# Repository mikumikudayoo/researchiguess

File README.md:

# TAPH research software

TAPH investigates flow-dependent blade-pitch control for hydropower generators.
The revised software implements a fixed fuzzy schedule, an HTTP controller,
**uncalibrated synthetic simulations**, a disabled-by-default ESP32 adapter and a
reproducible historical data analysis. It does not establish physical protection,
hydraulic efficiency, optimized pitch, longer component life or prototype readiness.

The researchers' design requirement is **increasing intended physical blade pitch
with increasing volumetric flow**. Servo rotation, actual blade pitch and angle of
attack are different quantities. The configurable affine linkage remains physically
unverified; a reversed linkage can require decreasing servo commands for increasing
pitch. The example identity transform is not a calibration.

## Install and verify

Use the Bun version pinned in `package.json` (1.4.3), Git, and a C++17-capable `g++`
for host-only firmware tests. TypeScript is pinned to 5.9.3. GitHub Actions runs the
same software checks on Ubuntu.

```sh
bun install --frozen-lockfile
bun test
bun run typecheck
bun run build
```

Build is a bundling check. Use the source-based commands below from the repository
root to run research workflows; generated bundles are not standalone deployment
packages with embedded source/data manifests. No test flashes firmware, opens a
serial device or energizes equipment. Passing tests verifies the stated software
specification, not physical calibration or scientific validation.

## Choose an explicit evidence pathway

Every output directory must be new. Generated files are excluded from Git by
`results/`; retain completed run directories and their manifests together.

```sh
# Historical software replay, preserving original arithmetic and timing defects:
bun run legacy:simulate -- results/my-legacy-replay

# New corrected constant-flow illustration:
bun run simulate -- results/my-corrected-constant-run

# New dynamic-flow comparisons and plots:
bun run simulate:dynamics -- results/my-dynamic-run

# Reanalysis of the unchanged historical manuscript table:
bun run analyze:historical --input /path/to/power-table.csv \
  --source-manifest /path/to/source-manifest.json --out results/my-historical-reanalysis
```

The constant and dynamic commands accept an optional second positional argument
containing a complete JSON configuration. Their generated `config.json` can serve
as an explicit starting point for a new run. Configurations, source and output
hashes, runtime and software revision are recorded. Do not analyze an incomplete
manifest or treat a dirty source tree as identified solely by its commit hash.

| Evidence category | Meaning |
|---|---|
| `historical-reported-unverified` | Locally supplied reported power values; physical versus simulation origin remains unresolved |
| `historical-simulator-replay` | New execution of the byte-preserved audited synthetic code; not proof of the historical table's source |
| `corrected-synthetic-simulation` | Newly generated outputs from explicit assumed model/scenario/controller configurations |
| `physical-measurement` | Reserved for future documented acquisitions with raw records, instruments and calibration; none supplied here |

Firmware status/acquisition telemetry is labeled unverified bench telemetry and
must not be promoted to a validated physical experiment without a separate run and
calibration record. See [data provenance and analysis](docs/reproducibility.md).

## Historical preservation and entry points

The inspected default branch matched audited commit
`a37d1d5abf4d13d775ae206b4cd1c4c59f0e88ce` exactly before these six development
milestones. No intervening historical change was found. All original files remain
in that immutable commit. Byte-identical server/simulator archives, baseline
constants, rule schedules, RNG behavior and all 25 replay CSV fingerprints are
preserved and tested. See [baseline inventory](docs/baseline.md).

The historical server commands 10°,25°,40°,58°,75° at the five nominal flows;
the historical simulator uses 70°,55°,40°,25°,10°. Those records are not changed.
`simulator.ts` now refuses ambiguous direct execution and points to the explicit
commands above. It does not silently substitute a new schedule into an old run.
Legacy CSV `Measured_RPM` is synthetic speed; historical `Generated_Wattage_W`
includes the unexplained additional 0.65 factor after terminal VI.

`bun server.ts` starts the new versioned controller API on localhost with the
unverified identity mapping and hardware eligibility false. The retired numeric-only
route returns 410. Server and new simulations call the same fixed zero-order
Sugeno-style schedule; they do not learn, adapt parameters or discover an optimum.
See [physical coordinates, memberships, rules and protocol](docs/controller.md).

## What the new simulations establish

The corrected electrical boundary uses `PL = VI = I²RL = V²/RL`, with internal
copper loss separate. The initial row is the initial state at t=0, followed by
exact first-order transitions for held targets and explicit measurement windows.
The assumed 42° speed peak is built into the default plant law, not experimentally
discovered. No hydraulic head, torque or closed mechanical energy balance is modeled.
See [constant model assumptions and schema](docs/model.md).

Dynamic scenarios prescribe constant, step, ramp and bounded profile flow. True
flow reaches the plant; separately noisy sampled flow reaches the controller.
Communication delay, actuator time constant and rate limit are uncalibrated
settings. Fixed5, fixed42, increasing fuzzy and increasing linear comparisons
share inputs, initial conditions and windows. Requested, delivered and actual
modeled pitch remain separate. See [dynamic assumptions and metric definitions](docs/dynamics.md).

Outputs include unit-labeled CSV/JSON and reproducible SVGs. Speed, power, energy,
variability and finite-record settling describe the model. Seeds and correlated
time points are not independent physical observations. The model cannot establish
wear, lifespan, overspeed protection, real-time hardware performance or efficiency.

## Historical table reanalysis

The public repository intentionally does not bundle manuscript data, private source
links or their acquisition records. Supply the exact CSV and source manifest locally
as described in [the input schema](docs/reproducibility.md). The tool preserves all
listed values, records byte hashes and produces descriptive tables, SD denominators,
plots and a conditional paired calculation on five flow means. It does not infer
physical provenance, independent sampling or preserved output from a nonsignificant
result. The 25 listed values per condition are described separately; column positions
are not verified trial IDs. Automated tests use explicitly artificial fixtures,
never invented research observations.

## Firmware boundary

The root `sketch_aug3a.ino` stops compilation and points to the separate target
`firmware/esp32/taph_reliability/`. Default configuration initializes serial status
only: no GPIO, sensor, network, servo or relay. The optional operational path needs
private reviewed configuration, calibration records, fresh eligible commands,
explicit local arming and a separate pump command. It never automatically starts
the pump. No zero-angle or hold-last behavior is declared safe.

Portable C++ tests and fake adapter interfaces verify software timing, message
validation, stale data, latching and actuator/pump sequencing. Both firmware paths
also compile with the pinned real ESP32 toolchain, using an illustrative target
and a non-production fixture. This establishes build compatibility only; the
as-built board, wiring, PWM startup, measured linkage, sensor calibration and
supervised bench validation remain unverified. See the versions, target and limits in
[firmware gates and remaining work](docs/firmware.md). The unrelated `badapple.ino`
demo remains unchanged and is not part of the TAPH sketch or validation.

## Review status and next work

Six stacked PRs propose these changes; they were not merged automatically. Review
the PR chain in order. The complete software/documentation/model versus physical
validation classification is in [engineering traceability](docs/engineering-traceability.md).

Before physical deployment, resolve the historical data source, as-built board and
wiring, measured command-to-pitch transform, sensor calibration, physically justified
fault action, external interlock and compile compatibility with the confirmed
as-built board. Then perform a supervised,
recorded bench protocol and a fair fixed-pitch sweep with a predefined speed/power
objective. Narrow claims to the evidence available while those steps remain open.

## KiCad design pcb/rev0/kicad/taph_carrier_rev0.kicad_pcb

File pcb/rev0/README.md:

# TAPH ESP32 carrier PCB: rev 0 preliminary design package

**Status: PRELIMINARY DESIGN FOR REVIEW. NOT FOR FABRICATION, ASSEMBLY OR ENERGIZATION.**
Prepared 2026-11-07 for the research adviser/consultant meeting on 2026-11-08. The board must not be
represented as manufacturable or safe to power until the actual components and this design have been
reviewed. A clean ERC/DRC is not proof of operational safety.

## What this is

A native, editable **KiCad 10** project for a modular two-layer carrier board. The board takes a socketed
classic-ESP32 development board (provisionally an Espressif ESP32-DevKitC V4, **to be confirmed**) and
provides:

* externally supplied low-voltage DC inputs, each a separate isolation point: logic, pump and servo;
* input protection and a 5 V regulator module for logic;
* a pump switch that is **off by hardware default**, with a hardware enable jumper;
* a buffered servo PWM output with its own supply entry;
* a flow sensor input plus optional RPM and pitch-feedback inputs;
* a generator voltage-sense input and a generator current-sensor interface (analog or I2C);
* separate pump current and pump supply-voltage measurement;
* an OLED (I2C) socket, I2C expansion and spare GPIO;
* 20 labelled test points.

No mains voltage is routed on the PCB, and generator power does not pass through it.

## Package contents

| Path | Content |
|---|---|
| `kicad/taph_carrier_rev0.kicad_pro` | KiCad project (open this) |
| `kicad/*.kicad_sch` | Hierarchical schematic: root architecture sheet + 7 block sheets |
| `kicad/taph_carrier_rev0.kicad_pcb` | Preliminary 2-layer layout (130 × 100 mm, provisional) |
| `kicad/libs/TAPH_Rev0.kicad_sym` | Project-local symbols for the two DevKitC header sockets (stock footprints) |
| `exports/taph_carrier_rev0_schematic.pdf` | **Schematic for review** (8 pages) |
| `exports/pcb/pcb_top_layers.png/.svg/.pdf`, `pcb_bottom_layers_mirrored.*`, `pcb_assembly_view_top.*` | 2-D layer views |
| `exports/pcb/render_top.png`, `render_bottom.png`, `render_iso.png` | 3-D renders (appearance only) |
| `exports/taph_carrier_rev0_kicad_bom.csv` | KiCad-exported grouped BOM with Status / candidate part / review-note fields |
| `exports/erc_report.txt`, `exports/drc_report.txt`, `exports/routing_report.json` | Verification output |
| `docs/architecture.md` | **Electrical architecture explanation** (domains, protection, default-off, front ends, layout status) |
| `docs/gpio_map.md` | **Proposed GPIO map** and the reasons for each pin |
| `docs/bom_review.md` / `.csv` | **Component list**, each part's status: implemented, provisional, TBD, optional, DNP or confirm |
| `docs/verification.md` | **ERC/DRC results**, blockers and assumptions that need physical confirmation |
| `docs/questions_for_review.md` | **Questions for the adviser and consultant** |
| `docs/review_log.md` | Review findings received (R1: independent review of PR #8) with technical responses and proposed, not yet applied, actions |
| `tools/` | Generators (`design.py` is the single source of design intent) and the build/export scripts |

## Designed versus conceptual

| Item | State |
|---|---|
| Schematic topology of every block | **Designed.** Electrically coherent; ERC 0 errors / 0 warnings; exported netlist verified pin-by-pin against intent |
| Logic power chain, ESP32 sockets, pump gate drive and default-off, servo buffer, pulse-input and ADC conditioning, I2C/OLED, test points | **Designed** with chosen values; candidate parts still need datasheet confirmation |
| Logic/signal/analog routing | **Preliminary.** All 38 non-blocked nets auto-routed by a simple project router; not hand-optimised |
| Board DRC | **Not clean.** 35 unconnected items (blocked pump/servo nets), 4 starved-thermal errors and 2 silkscreen warnings remain open (`docs/verification.md`) |
| Pump power path, servo power path | **Placed, routing BLOCKED.** Widths, fuses, MOSFET and shunt depend on unmeasured currents |
| Generator voltage divider, shunt value, INA180 gain, fuse ratings, servo bulk capacitor, TVS on servo/generator inputs | **TBD** (placeholder values); blocked on external specifications |
| RPM and pitch-feedback inputs, I2C expansion, spare GPIO | **Optional** interfaces; sensors not chosen |
| Mechanical safe state of the blade/servo; generator electrical characteristics | **Conceptual / unresolved.** Not claimed by this board |
| Dev board identity, pinout, row spacing, antenna position; enclosure and mounting | **To be confirmed** physically |
| Firmware support for the new channels and this GPIO map | **Not started.** The existing firmware is unchanged |

## Reference sources and how they were used

* **Rev-0 architecture:** the requirement list in the research director's brief of 2026-11-07. A separate
  "PCB architecture rev 0" file is not present in the repository. See `docs/architecture.md` §1.
* **Historical firmware** (`sketch_aug3a.ino` at `a37d1d5`): an inventory of functions only. Its pin
  assignments are not treated as evidence of wiring; several are strapping pins and were changed.
* **Current reliability adapter** (`firmware/esp32/taph_reliability`): interface requirements (pull-up
  pulse input, raw ADC current, reviewed inactive pump level, servo PWM). Its pins stay unconfigured.
* **Tinkercad conceptual drawing:** described in audit finding F10 (Uno with substitute symbols, such
  as a PIR for the flow sensor). Treated as a conceptual block list only; its wires are not authoritative.

## Reproduce

Requires KiCad 10 (`kicad-cli` and KiCad's bundled Python with `pcbnew`) and Python 3 for the
schematic generator:

```bash
bash pcb/rev0/tools/build.sh
```

```bash
bash pcb/rev0/tools/export.sh
```

`build.sh` regenerates the symbols, project, schematic and board from `tools/design.py` and
`tools/gen_pcb.py`, then runs ERC, the netlist cross-check and DRC. The generators are deterministic
(stable UUIDs). If the design is edited by hand in KiCad, treat the KiCad files as the source of truth and
stop regenerating them.

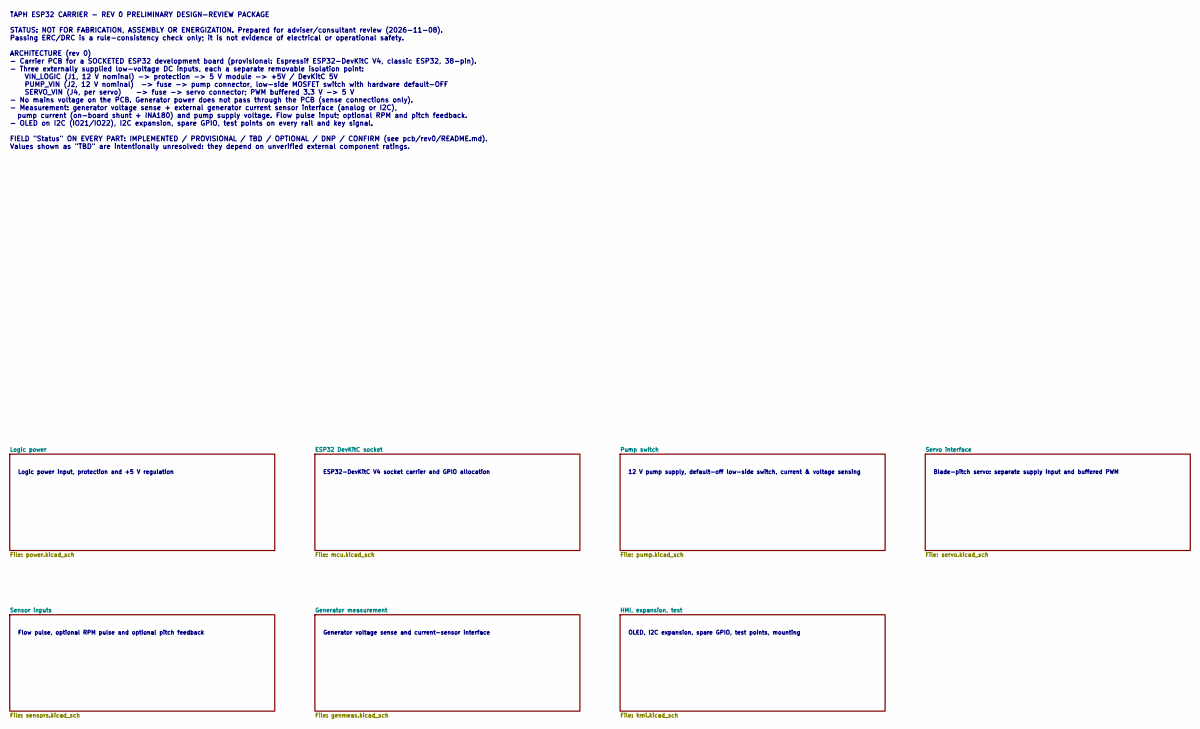
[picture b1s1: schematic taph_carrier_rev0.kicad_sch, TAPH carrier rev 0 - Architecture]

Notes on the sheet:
TAPH ESP32 CARRIER - REV 0 PRELIMINARY DESIGN-REVIEW PACKAGE STATUS: NOT FOR FABRICATION, ASSEMBLY OR ENERGIZATION. Prepared for adviser/consultant review (2026-11-08). Passing ERC/DRC is a rule-consistency check only; it is not evidence of electrical or operational safety. ARCHITECTURE (rev 0) - C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
Logic power input, protection and +5 V regulation
ESP32-DevKitC V4 socket carrier and GPIO allocation
12 V pump supply, default-off low-side switch, current & voltage sensing
Blade-pitch servo: separate supply input and buffered PWM
Flow pulse, optional RPM pulse and optional pitch feedback
Generator voltage sense and current-sensor interface
OLED, I2C expansion, spare GPIO, test points, mounting

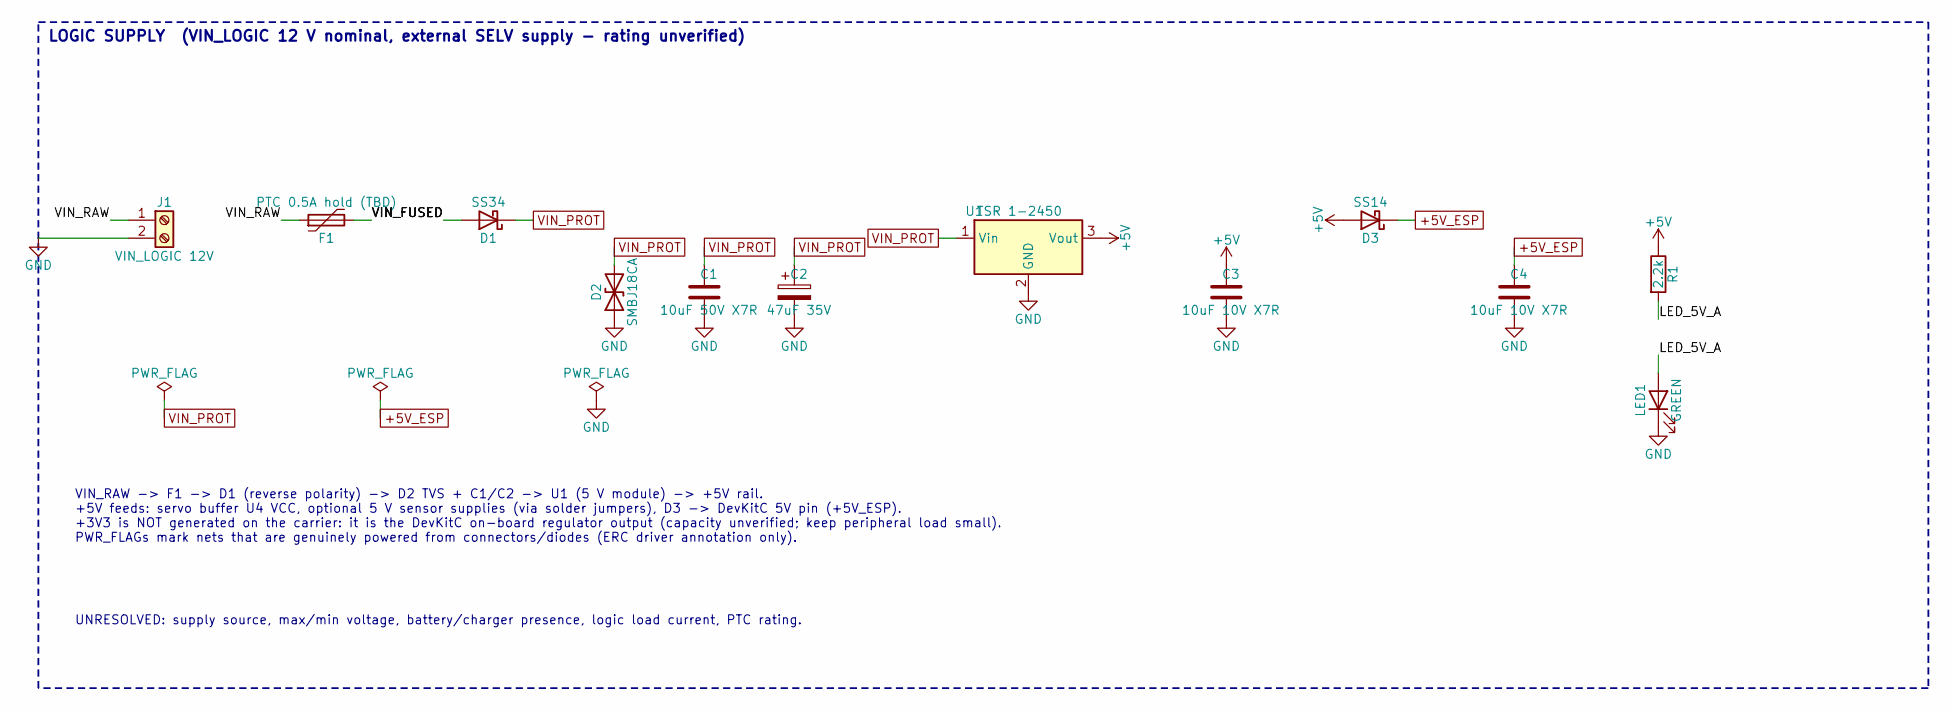
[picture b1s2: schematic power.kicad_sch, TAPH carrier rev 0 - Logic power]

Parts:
C1: 10uF 50V X7R; C_1210_3225Metric
C2: 47uF 35V; CP_Elec_6.3x7.7
C3, C4: 10uF 10V X7R; C_1206_3216Metric
D1: SS34; D_SMA; MPN_candidate SS34 (candidate, 40 V 3 A class - verif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
D2: SMBJ18CA; D_SMB; MPN_candidate SMBJ18CA (candidate - verify clamp vs U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
D3: SS14; D_SMA; MPN_candidate SS14 (candidate)
F1: PTC 0.5A hold (TBD); Fuse_1812_4532Metric
J1: VIN_LOGIC 12V; TerminalBlock_Phoenix_MKDS-1,5-2-5.08_1x02_P5.08mm_Horizont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; MPN_candidate Phoenix MKDS 1,5/2-5,08 (candidate)
LED1: GREEN; LED_0805_2012Metric
R1: 2.2k; R_0805_2012Metric
U1: TSR 1-2450; Converter_DCDC_TRACO_TSR-1_THT; MPN_candidate TRACO TSR 1-2450 (candidate)

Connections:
+5V: C3.1, D3.2 (A), R1.1, U1.3 (Vout); also elsewhere on the board
+5V_ESP: C4.1, D3.1 (K); also elsewhere on the board
/Logic power/LED_5V_A: LED1.2 (A), R1.2
/Logic power/VIN_FUSED: D1.2 (A), F1.2
/Logic power/VIN_RAW: F1.1, J1.1
GND: C1.2, C2.2, C3.2, C4.2, D2.1 (A1), J1.2, LED1.1 (K), U1.2 (GND); also elsewhere on the board
VIN_PROT: C1.1, C2.1, D1.1 (K), D2.2 (A2), U1.1 (Vin); also elsewhere on the board

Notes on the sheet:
LOGIC SUPPLY (VIN_LOGIC 12 V nominal, external SELV supply - rating unverified)
VIN_RAW -> F1 -> D1 (reverse polarity) -> D2 TVS + C1/C2 -> U1 (5 V module) -> +5V rail. +5V feeds: servo buffer U4 VCC, optional 5 V sensor supplies (via solder jumpers), D3 -> DevKitC 5V pin (+5V_ESP). +3V3 is NOT generated on the carrier: it is the DevKitC on-board regulator output (capacity unv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
UNRESOLVED: supply source, max/min voltage, battery/charger presence, logic load current, PTC rating.

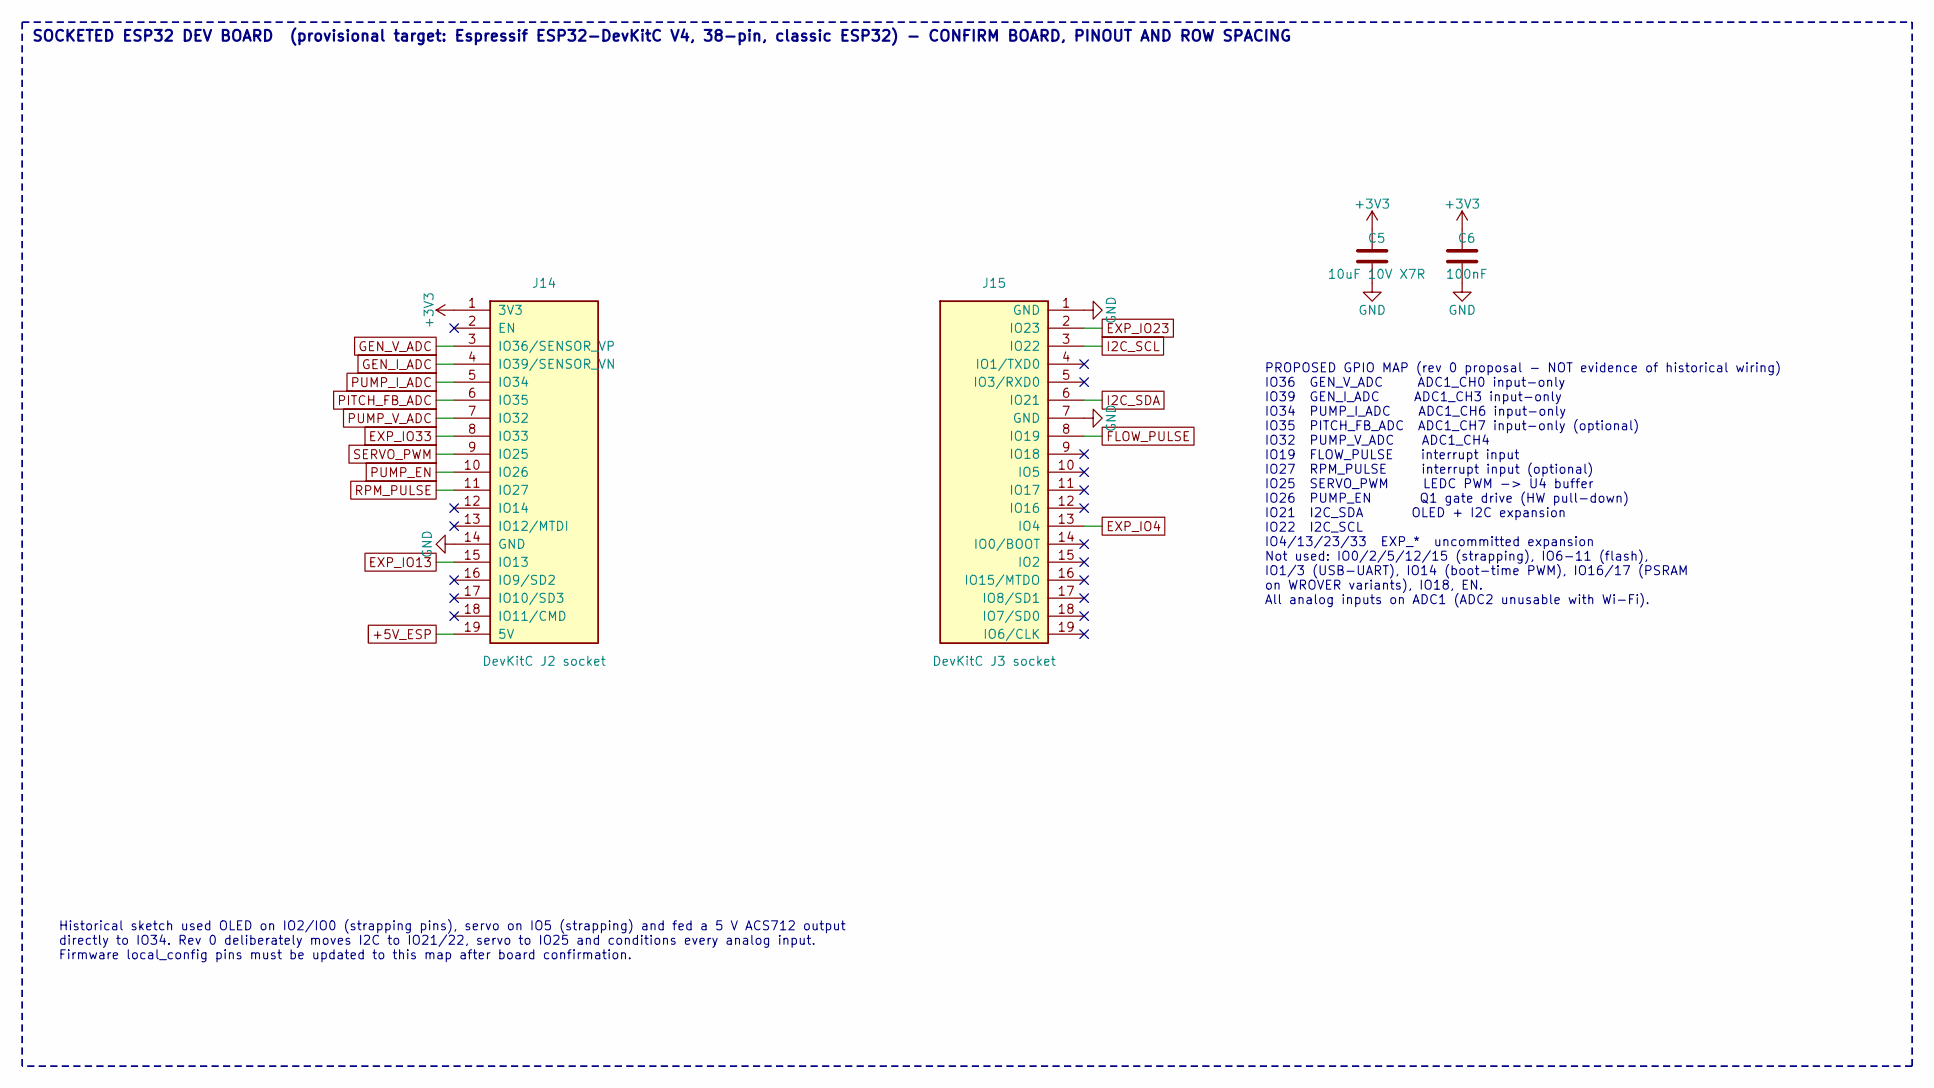
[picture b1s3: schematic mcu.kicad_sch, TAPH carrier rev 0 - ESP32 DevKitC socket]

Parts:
C5: 10uF 10V X7R; C_1206_3216Metric
C6: 100nF; C_0805_2012Metric
J14: DevKitC J2 socket; PinSocket_1x19_P2.54mm_Vertical; MPN_candidate 2.54 mm 1x19 female header
J15: DevKitC J3 socket; PinSocket_1x19_P2.54mm_Vertical; MPN_candidate 2.54 mm 1x19 female header

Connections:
+3V3: C5.1, C6.1, J14.1 (3V3); also elsewhere on the board
+5V_ESP: J14.19 (5V); also elsewhere on the board
EXP_IO4: J15.13 (IO4); also elsewhere on the board
EXP_IO13: J14.15 (IO13); also elsewhere on the board
EXP_IO23: J15.2 (IO23); also elsewhere on the board
EXP_IO33: J14.8 (IO33); also elsewhere on the board
FLOW_PULSE: J15.8 (IO19); also elsewhere on the board
GEN_I_ADC: J14.4 (IO39/SENSOR_VN); also elsewhere on the board
GEN_V_ADC: J14.3 (IO36/SENSOR_VP); also elsewhere on the board
GND: C5.2, C6.2, J14.14 (GND), J15.1 (GND), J15.7 (GND); also elsewhere on the board
I2C_SCL: J15.3 (IO22); also elsewhere on the board
I2C_SDA: J15.6 (IO21); also elsewhere on the board
PITCH_FB_ADC: J14.6 (IO35); also elsewhere on the board
PUMP_EN: J14.10 (IO26); also elsewhere on the board
PUMP_I_ADC: J14.5 (IO34); also elsewhere on the board
PUMP_V_ADC: J14.7 (IO32); also elsewhere on the board
RPM_PULSE: J14.11 (IO27); also elsewhere on the board
SERVO_PWM: J14.9 (IO25); also elsewhere on the board

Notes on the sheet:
SOCKETED ESP32 DEV BOARD (provisional target: Espressif ESP32-DevKitC V4, 38-pin, classic ESP32) - CONFIRM BOARD, PINOUT AND ROW SPACING
PROPOSED GPIO MAP (rev 0 proposal - NOT evidence of historical wiring) IO36 GEN_V_ADC ADC1_CH0 input-only IO39 GEN_I_ADC ADC1_CH3 input-only IO34 PUMP_I_ADC ADC1_CH6 input-only IO35 PITCH_FB_ADC ADC1_CH7 input-only (optional) IO32 PUMP_V_ADC ADC1_CH4 IO19 FLOW_PULSE interrupt input IO27 RPM_PULSE i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
Historical sketch used OLED on IO2/IO0 (strapping pins), servo on IO5 (strapping) and fed a 5 V ACS712 output directly to IO34. Rev 0 deliberately moves I2C to IO21/22, servo to IO25 and conditions every analog input. Firmware local_config pins must be updated to this map after board confirmation.

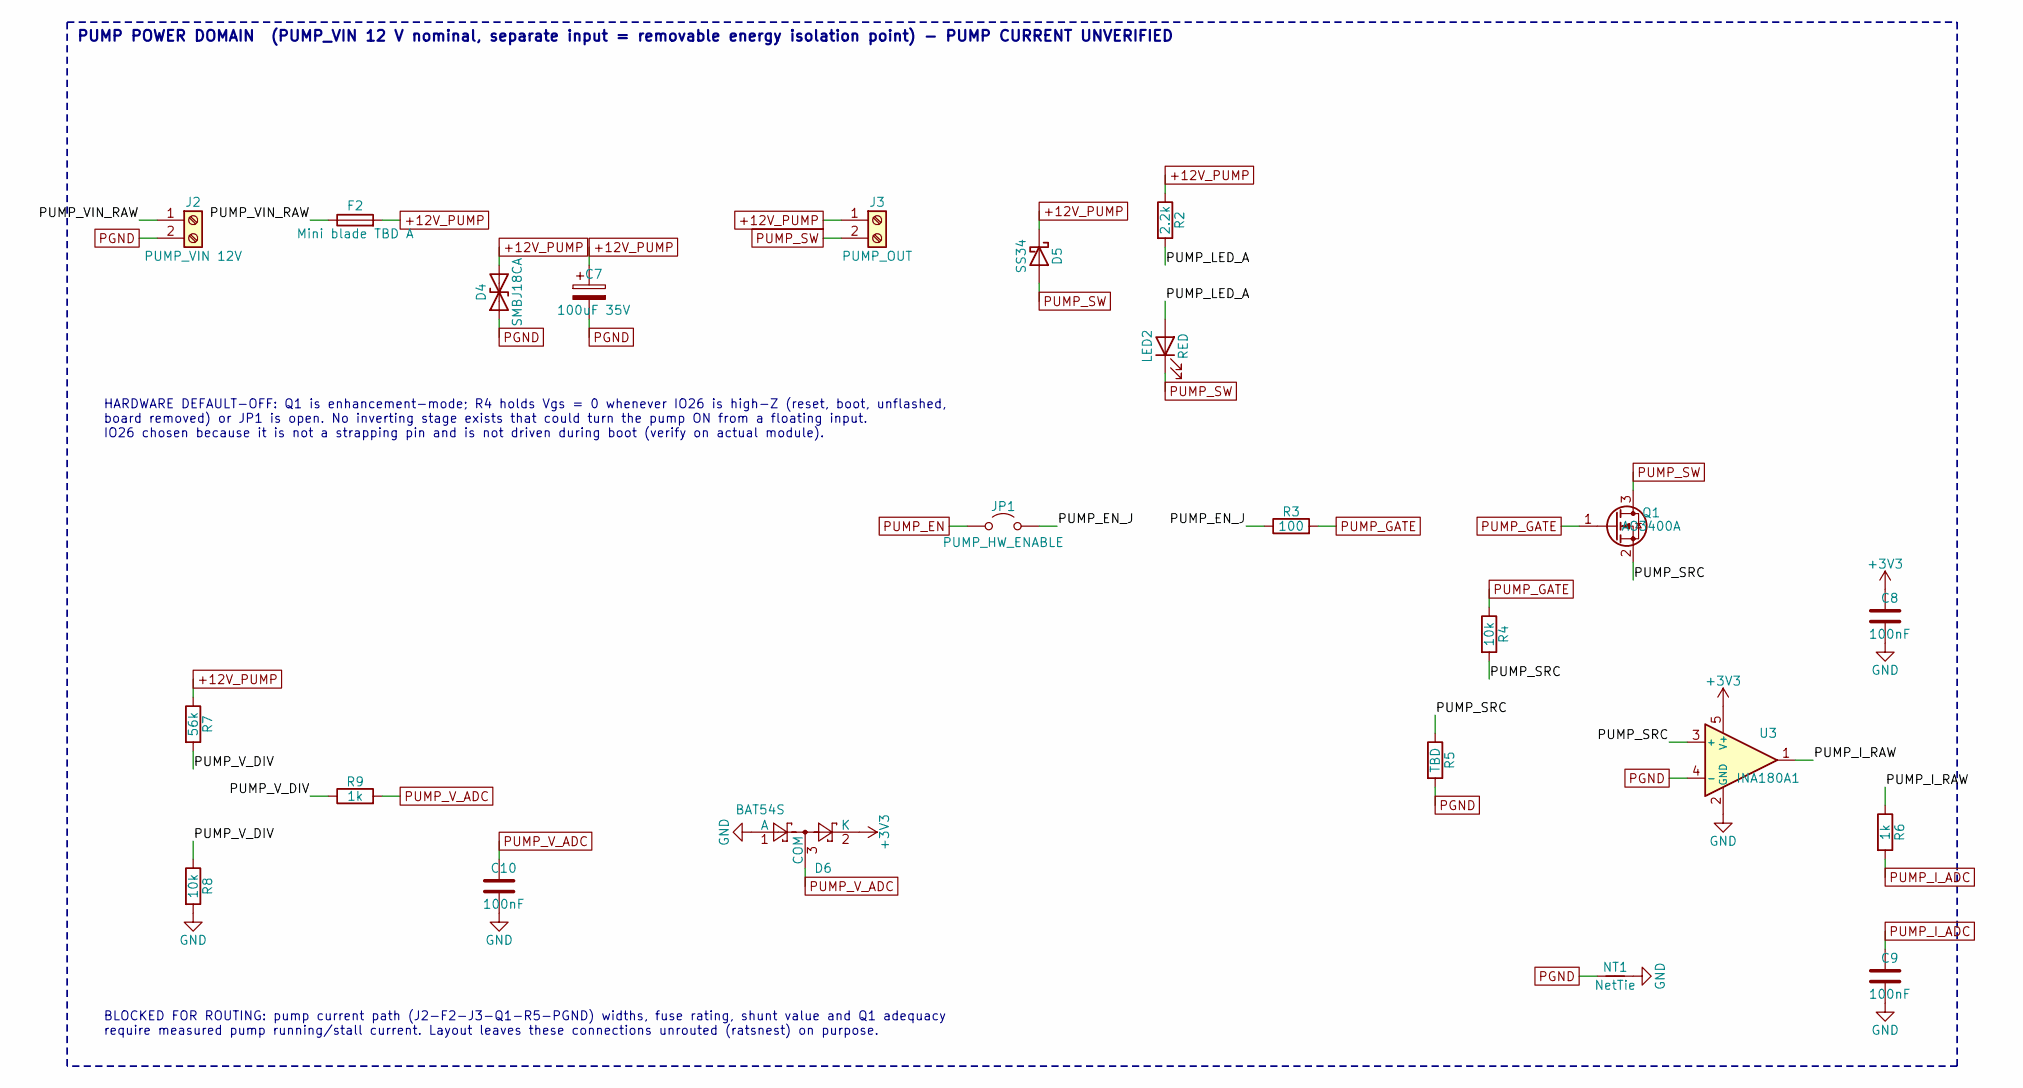
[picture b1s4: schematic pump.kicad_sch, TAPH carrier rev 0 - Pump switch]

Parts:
C7: 100uF 35V; CP_Elec_8x10
C8, C9, C10: 100nF; C_0805_2012Metric
D4: SMBJ18CA; D_SMB; MPN_candidate SMBJ18CA (candidate)
D5: SS34; D_SMA; MPN_candidate SS34 (candidate)
D6: BAT54S; SOT-23; MPN_candidate BAT54S (candidate)
F2: Mini blade TBD A; Fuseholder_Blade_Mini_Keystone_3568; MPN_candidate Keystone 3568 holder (candidate)
J2: PUMP_VIN 12V; TerminalBlock_Phoenix_MKDS-1,5-2-5.08_1x02_P5.08mm_Horizont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; MPN_candidate Phoenix MKDS 1,5/2-5,08 (candidate)
J3: PUMP_OUT; TerminalBlock_Phoenix_MKDS-1,5-2-5.08_1x02_P5.08mm_Horizont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; MPN_candidate Phoenix MKDS 1,5/2-5,08 (candidate)
JP1: PUMP_HW_ENABLE; PinHeader_1x02_P2.54mm_Vertical; MPN_candidate 2-pin header + shunt
LED2: RED; LED_0805_2012Metric
NT1: NetTie; NetTie-2_SMD_Pad2.0mm
Q1: AO3400A; SOT-23; MPN_candidate AO3400A (candidate)
R2: 2.2k; R_0805_2012Metric
R3: 100; R_0805_2012Metric
R4, R8: 10k; R_0805_2012Metric
R5: TBD; R_2512_6332Metric
R6, R9: 1k; R_0805_2012Metric
R7: 56k; R_0805_2012Metric
U3: INA180A1; SOT-23-5; MPN_candidate TI INA180A1 (candidate)

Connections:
+3V3: C8.1, D6.2 (K), U3.5 (V+); also elsewhere on the board
+12V_PUMP: C7.1, D4.2 (A2), D5.1 (K), F2.2, J3.1, R2.1, R7.1; also elsewhere on the board
/Pump switch/PUMP_EN_J: JP1.2 (B), R3.1
/Pump switch/PUMP_I_RAW: R6.1, U3.1
/Pump switch/PUMP_LED_A: LED2.2 (A), R2.2
/Pump switch/PUMP_SRC: Q1.2 (S), R4.2, R5.1, U3.3 (+)
/Pump switch/PUMP_VIN_RAW: F2.1, J2.1
/Pump switch/PUMP_V_DIV: R7.2, R8.1, R9.1
GND: C8.2, C9.2, C10.2, D6.1 (A), NT1.2, R8.2, U3.2 (GND); also elsewhere on the board
PGND: C7.2, D4.1 (A1), J2.2, NT1.1, R5.2, U3.4 (-); also elsewhere on the board
PUMP_EN: JP1.1 (A); also elsewhere on the board
PUMP_GATE: Q1.1 (G), R3.2, R4.1; also elsewhere on the board
PUMP_I_ADC: C9.1, R6.2; also elsewhere on the board
PUMP_SW: D5.2 (A), J3.2, LED2.1 (K), Q1.3 (D); also elsewhere on the board
PUMP_V_ADC: C10.1, D6.3 (COM), R9.2; also elsewhere on the board

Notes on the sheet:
PUMP POWER DOMAIN (PUMP_VIN 12 V nominal, separate input = removable energy isolation point) - PUMP CURRENT UNVERIFIED
HARDWARE DEFAULT-OFF: Q1 is enhancement-mode; R4 holds Vgs = 0 whenever IO26 is high-Z (reset, boot, unflashed, board removed) or JP1 is open. No inverting stage exists that could turn the pump ON from a floating input. IO26 chosen because it is not a strapping pin and is not driven during boot (ve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
BLOCKED FOR ROUTING: pump current path (J2-F2-J3-Q1-R5-PGND) widths, fuse rating, shunt value and Q1 adequacy require measured pump running/stall current. Layout leaves these connections unrouted (ratsnest) on purpose.

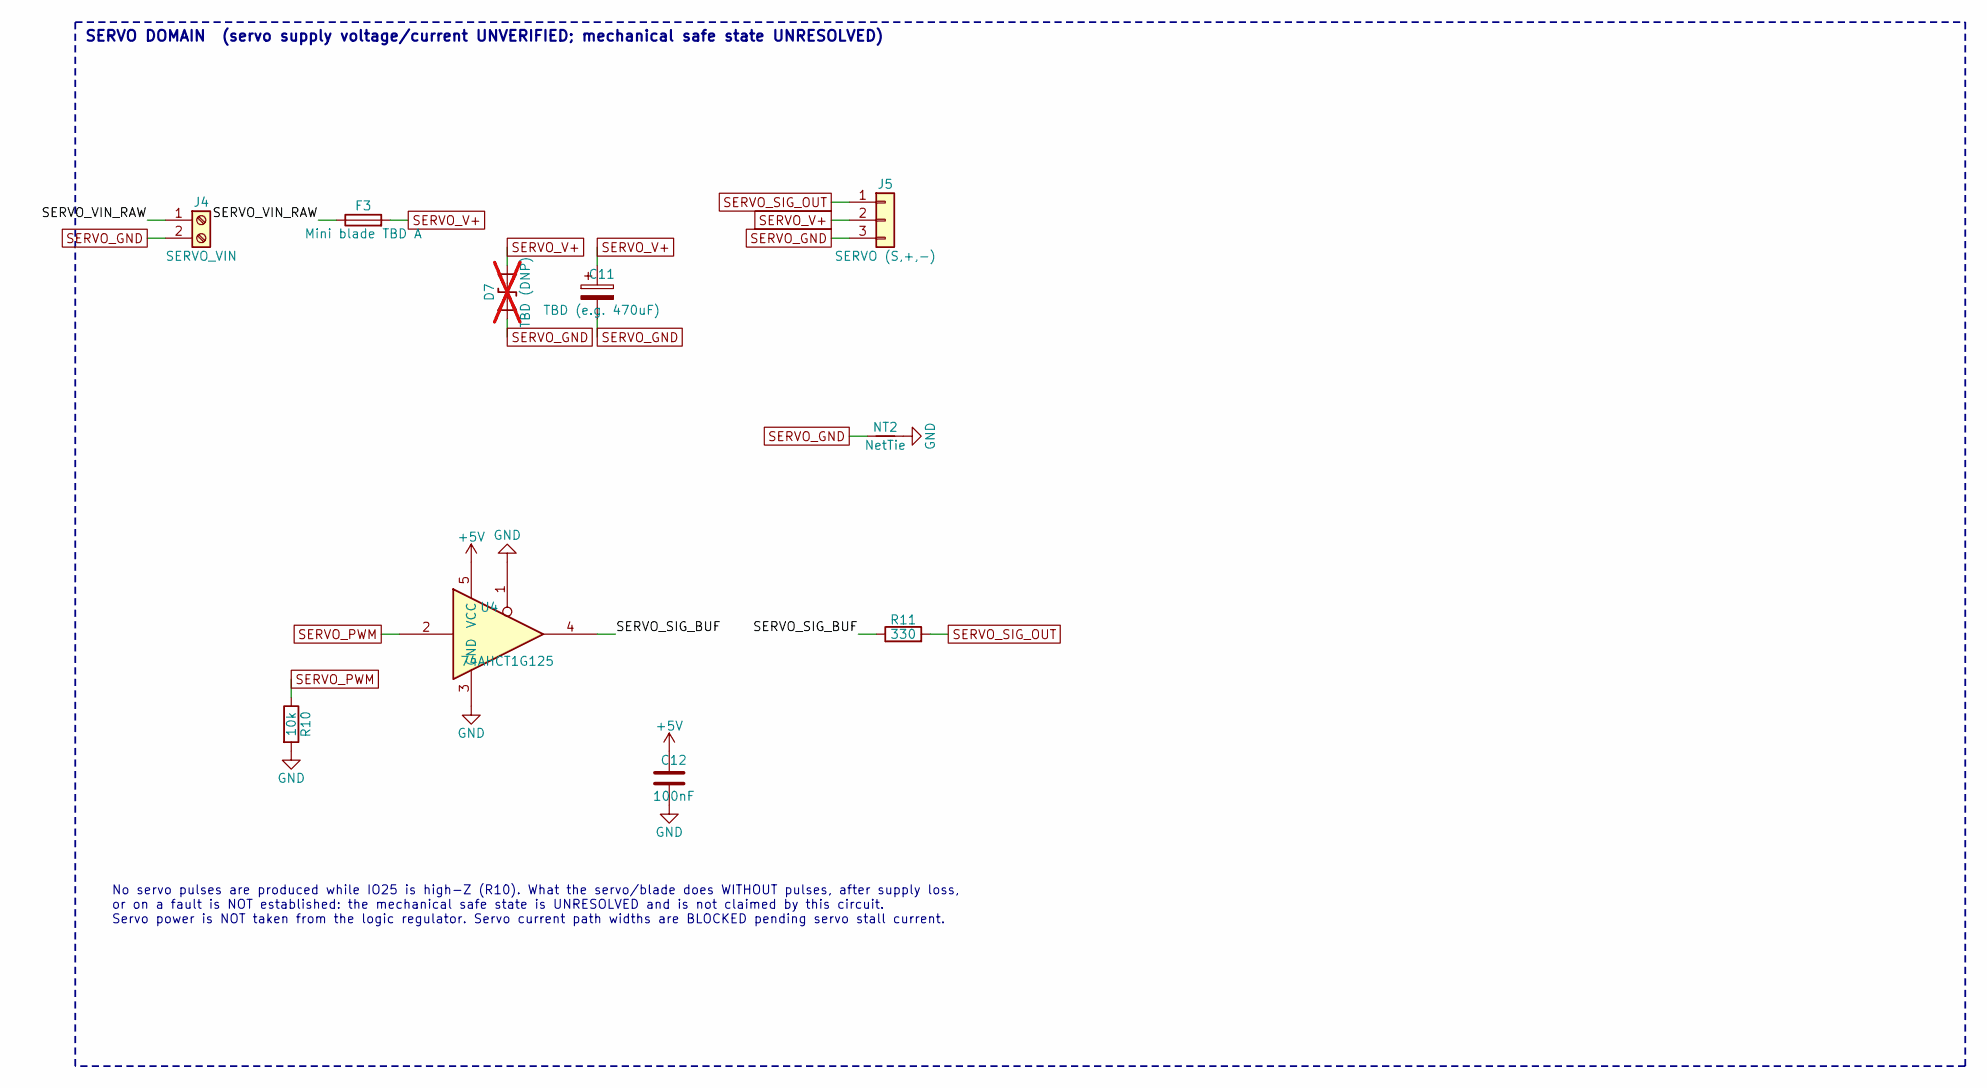
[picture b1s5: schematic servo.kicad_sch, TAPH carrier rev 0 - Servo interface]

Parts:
C11: TBD (e.g. 470uF); CP_Elec_8x10
C12: 100nF; C_0805_2012Metric
D7: TBD (DNP); D_SMB; not fitted
F3: Mini blade TBD A; Fuseholder_Blade_Mini_Keystone_3568; MPN_candidate Keystone 3568 holder (candidate)
J4: SERVO_VIN; TerminalBlock_Phoenix_MKDS-1,5-2-5.08_1x02_P5.08mm_Horizont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; MPN_candidate Phoenix MKDS 1,5/2-5,08 (candidate)
J5: SERVO (S,+,-); PinHeader_1x03_P2.54mm_Vertical
NT2: NetTie; NetTie-2_SMD_Pad2.0mm
R10: 10k; R_0805_2012Metric
R11: 330; R_0805_2012Metric
U4: 74AHCT1G125; SOT-23-5; MPN_candidate 74AHCT1G125 SOT-23-5 (candidate)

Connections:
+5V: C12.1, U4.5 (VCC); also elsewhere on the board
/Servo interface/SERVO_SIG_BUF: R11.1, U4.4
/Servo interface/SERVO_VIN_RAW: F3.1, J4.1
GND: C12.2, NT2.2, R10.2, U4.1, U4.3 (GND); also elsewhere on the board
SERVO_GND: C11.2, D7.1 (A1), J4.2, J5.3, NT2.1; also elsewhere on the board
SERVO_PWM: R10.1, U4.2; also elsewhere on the board
SERVO_SIG_OUT: J5.1, R11.2; also elsewhere on the board
SERVO_V+: C11.1, D7.2 (A2), F3.2, J5.2; also elsewhere on the board

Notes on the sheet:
SERVO DOMAIN (servo supply voltage/current UNVERIFIED; mechanical safe state UNRESOLVED)
No servo pulses are produced while IO25 is high-Z (R10). What the servo/blade does WITHOUT pulses, after supply loss, or on a fault is NOT established: the mechanical safe state is UNRESOLVED and is not claimed by this circuit. Servo power is NOT taken from the logic regulator. Servo current path w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

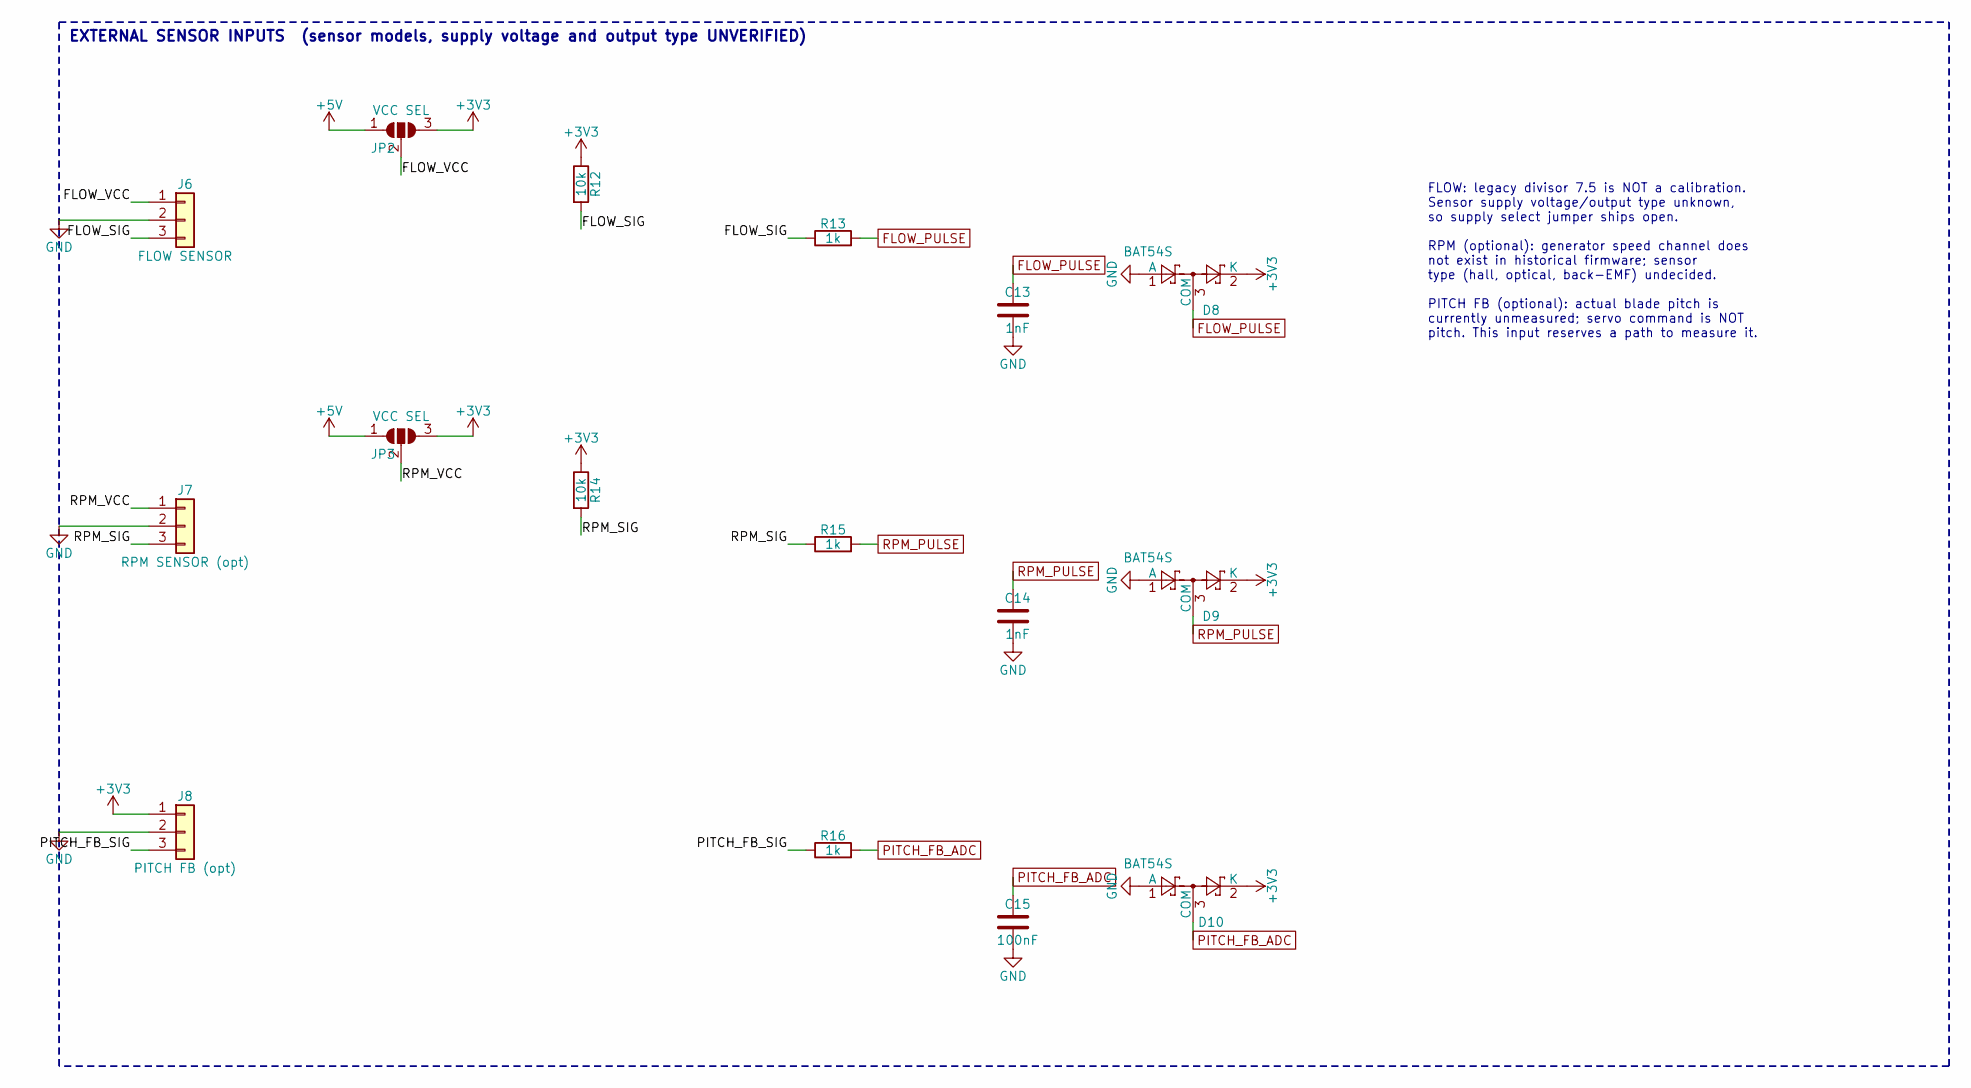
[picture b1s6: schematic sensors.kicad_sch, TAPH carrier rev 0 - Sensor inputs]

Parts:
C13, C14: 1nF; C_0805_2012Metric
C15: 100nF; C_0805_2012Metric
D8, D9, D10: BAT54S; SOT-23; MPN_candidate BAT54S (candidate)
J6: FLOW SENSOR; JST_XH_B3B-XH-A_1x03_P2.50mm_Vertical; MPN_candidate JST XH 3-pin (candidate)
J7: RPM SENSOR (opt); JST_XH_B3B-XH-A_1x03_P2.50mm_Vertical; MPN_candidate JST XH 3-pin (candidate)
J8: PITCH FB (opt); JST_XH_B3B-XH-A_1x03_P2.50mm_Vertical; MPN_candidate JST XH 3-pin (candidate)
JP2, JP3: VCC SEL; SolderJumper-3_P1.3mm_Open_RoundedPad1.0x1.5mm
R12, R14: 10k; R_0805_2012Metric
R13, R15, R16: 1k; R_0805_2012Metric

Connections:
+3V3: D8.2 (K), D9.2 (K), D10.2 (K), J8.1, JP2.3 (B), JP3.3 (B), R12.1, R14.1; also elsewhere on the board
+5V: JP2.1 (A), JP3.1 (A); also elsewhere on the board
/Sensor inputs/FLOW_SIG: J6.3, R12.2, R13.1
/Sensor inputs/FLOW_VCC: J6.1, JP2.2 (C)
/Sensor inputs/PITCH_FB_SIG: J8.3, R16.1
/Sensor inputs/RPM_SIG: J7.3, R14.2, R15.1
/Sensor inputs/RPM_VCC: J7.1, JP3.2 (C)
FLOW_PULSE: C13.1, D8.3 (COM), R13.2; also elsewhere on the board
GND: C13.2, C14.2, C15.2, D8.1 (A), D9.1 (A), D10.1 (A), J6.2, J7.2, J8.2; also elsewhere on the board
PITCH_FB_ADC: C15.1, D10.3 (COM), R16.2; also elsewhere on the board
RPM_PULSE: C14.1, D9.3 (COM), R15.2; also elsewhere on the board

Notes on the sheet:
EXTERNAL SENSOR INPUTS (sensor models, supply voltage and output type UNVERIFIED)
FLOW: legacy divisor 7.5 is NOT a calibration. Sensor supply voltage/output type unknown, so supply select jumper ships open. RPM (optional): generator speed channel does not exist in historical firmware; sensor type (hall, optical, back-EMF) undecided. PITCH FB (optional): actual blade pitch is cu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
